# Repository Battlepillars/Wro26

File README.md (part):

<div align="left">

# Table of contents

<ul dir="auto">
    <li><details><summary><a href="#the-team">The team</a></summary>
        <ul dir="auto">
            <li><a href="#nils-stauff">Nils Stauff</a></li>
            <li><a href="#olivia-greilich">Olivia Greilich</a></li>
            <li><a href="#anton-wiesen">Anton Wiesen</a></li>
            <li><a href="#team-photo">Team photo</a></li>
        </ul>
        </details>
      </li>
    <li><a href="#videos-of-the-robot">Videos of the robot</a></li>
    <li><details><summary><a href="#mobility-and-mechanics">1. Mobility and mechanics</a></summary>
        <ul dir="auto">
            <li><a href="#development-goal">Development goal</a></li>
            <li><a href="#chassis-and-mechanical-structure">Chassis and mechanical structure</a>
              <ul dir="auto">
                <li><a href="#chassis-design">Chassis design</a></li>
                <li><a href="#base-deck-iteration">Base deck iteration</a></li>
                <li><a href="#chassis-structure">Chassis structure</a></li>
              </ul>
            </li>
            <li><a href="#drivetrain-concept-and-motor-selection">Drivetrain concept and motor selection</a></li>
            <li><a href="#rear-axle-and-differential">Rear axle and differential</a></li>
            <li><a href="#front-axle-and-steering">Front axle and steering</a>
              <ul dir="auto">
                <li><a href="#ackermann-condition-in-our-steering">Ackermann condition in our steering</a></li>
                <li><a href="#mechanical-precision-of-our-steering">Mechanical precision of our steering</a></li>
                <li><a href="#front-axle-rims-and-tires">Front axle rims and tires</a></li>
              </ul>
            </li>
            <li><a href="#servo-selection-and-position">Servo selection and position</a>
              <ul dir="auto">
                <li><a href="#servo-selection">Servo selection</a></li>
                <li><a href="#servo-position">Servo position</a></li>
              </ul>
            </li>
          </ul>
          </details>
        </li>
        <li><details><summary><a href="#power-and-sensors">2. Power and sensors</a></summary>
        <ul dir="auto">
            <li><a href="#concept">Concept</a></li>
            <li><a href="#electronics-setup">Electronics setup</a></li>
            <li><a href="#camera-use-of-the-camera-and-calibration">Camera: use of the camera and calibration</a>
              <ul dir="auto">
                <li><a href="#use-of-the-camera">Use of the camera</a></li>
                <li><a href="#further-development-rotating-camera-tower">Further development: rotating camera tower</a></li>
                <li><a href="#calibration-procedure">Calibration procedure</a></li>
              </ul>
            </li>
            <li><a href="#distance-sensors">Distance sensors</a>
                <ul dir="auto">
                    <li><a href="#selection-of-distance-sensors">Selection of distance sensors</a></li>
                    <li><a href="#sensor-evaluation">Sensor evaluation</a></li>
                    <li><a href="#sensor-placement-in-the-robot">Sensor placement in the robot</a></li>
                </ul>
            </li>
            <li><a href="#gyro">Gyro</a></li>
            <li><a href="#power-budget-power-supply-and-consumption">Power budget: power supply and consumption</a>
                <ul dir="auto">
                    <li><a href="#worst-case-peak-current-and-regulator-sizing">Worst-case peak current and regulator sizing</a></li>
                    <li><a href="#measured-total-power-requirement">Measured total power requirement</a></li>
                    <li><a href="#runtime-calculation">Runtime calculation</a></li>
                    <li><a href="#avoiding-deep-discharge">Avoiding deep discharge</a></li>
                    <li><a href="#voltage-supply-of-the-individual-components">Voltage supply of the individual components</a></li>
                    <li><a href="#failure-modes-in-sensors-and-power-supply">Failure modes in sensors and power supply</a></li>
                </ul>
            </li>
          </ul>
          </details>
        </li>
        <li><details><summary><a href="#software-development">3. Software development</a></summary>
        <ul dir="auto">
            <li><a href="#software-architecture">Software architecture</a></li>
            <li><a href="#threading-and-system-flow">Threading and system flow</a></li>
            <li><a href="#driving-primitives-in-drivecontrollerpy">Driving primitives in driveController.py</a></li>
            <li><a href="#opening-challenge-driving-strategy">Opening challenge driving strategy</a></li>
            <li><a href="#obstacle-challenge-driving-strategy---strategy-change">Obstacle challenge driving strategy - strategy change</a>
              <ul dir="auto">
                <li><a href="#old-strategy-scanning-while-driving">Old strategy: scanning while driving</a></li>
                <li><a href="#new-strategy-full-scan-fixed-route">New strategy: full scan, fixed route</a></li>
                <li><a href="#passing-two-obstacles-in-one-section">Passing two obstacles in one section</a></li>
                <li><a href="#parking-and-un-parking">Parking and un-parking</a></li>
              </ul>
            </li>
            <li><a href="#serial-communication-and-data-model">Serial communication and data model</a></li>
            <li><a href="#camera-processing">Camera processing</a>
              <ul dir="auto">
                <li><a href="#mask-pipeline">Mask pipeline</a></li>
              </ul>
            </li>
            <li><a href="#software-improvements">Software improvements</a></li>
          </ul>
          </details>
        </li>
        <li><details><summary><a href="#overall-robot-system-and-technical-decisions">4. Overall robot system and technical decisions</a></summary>
        <ul dir="auto">
            <li><a href="#design-constraints">Design constraints</a></li>
            <li><a href="#system-level-risks">System-level risks</a></li>
            <li><a href="#our-robot">Our robot</a></li>
            <li><a href="#technical-specifications">Technical specifications</a></li>
            <li><a href="#system-architecture">System architecture</a></li>
            <li><a href="#key-technical-decisions">Key technical decisions</a>
              <ul dir="auto">
                <li><a href="#raspberry-pi-vs-pure-microcontroller">Raspberry Pi vs. pure microcontroller</a></li>
                <li><a href="#raspberry-pi-5-vs-raspberry-pi-cm5">Raspberry Pi 5 vs. Raspberry Pi CM5</a></li>
                <li><a href="#lidar-vs-time-of-flight-sensors--control-paradigm">LiDAR vs. time-of-flight sensors / control paradigm</a></li>
                <li><a href="#camera-height-and-detection-strategy">Camera height and detection strategy</a></li>
                <li><a href="#chassis-material-pla-vs-ppa-cf">Chassis material: PLA vs. PPA-CF</a></li>
                <li><a href="#gyro-bno055-with-and-without-magnetometer-vs-bno086-without-magnetometer">Gyro: BNO055 with and without magnetometer vs. BNO086 without magnetometer</a></li>
                <li><a href="#rear-axle-ball-differential-vs-rigid-axle">Rear axle: ball differential vs. rigid axle</a></li>
                <li><a href="#tof-sensor-vl53l8cx-vs-tmf8828">ToF sensor: VL53L8CX vs. TMF8828</a></li>
              </ul>
            </li>
            <li><a href="#development-milestones">Development milestones</a></li>
          </ul>
          </details>
        </li>
        <li><details><summary><a href="#5-construction-guide">5. Construction guide</a></summary>
        <ul dir="auto">
            <li><a href="#assembly-overview">Assembly overview</a></li>
            <li><a href="#step-1-preparing-the-3d-printed-parts">Step 1: Preparing the 3D-printed parts</a></li>
            <li><a href="#step-2-lower-deck-assembly">Step 2: Lower deck assembly</a>
              <ul dir="auto">
                <li><a href="#21-drive-motor-and-rear-axle-bearings">2.1 Drive motor and rear-axle bearings</a></li>
                <li><a href="#22-front-axle--steering-knuckles">2.2 Front axle / steering knuckles</a></li>
                <li><a href="#23-rear-axle-front-wheels-and-steering-linkage">2.3 Rear axle, front wheels and steering linkage</a></li>
              </ul>
            </li>
            <li><a href="#step-3-middle-deck-assembly">Step 3: Middle deck assembly</a>
              <ul dir="auto">
                <li><a href="#31-support-bridge-and-middle-deck">3.1 Support bridge and middle deck</a></li>
                <li><a href="#32-mount-the-baseboard-and-connect-all-components">3.2 Mount the baseboard and connect all components</a></li>
              </ul>
            </li>
            <li><a href="#step-4-upper-deck--tof-sensors-and-rotating-camera-tower">Step 4: Upper deck – ToF sensors and rotating camera tower</a>
              <ul dir="auto">
                <li><a href="#41-mount-the-upper-deck">4.1 Mount the upper deck</a></li>
                <li><a href="#42-insert-the-distance-sensors">4.2 Insert the distance sensors</a></li>
                <li><a href="#43-mount-the-camera-tower-and-camera">4.3 Mount the camera tower and camera</a></li>
                <li><a href="#44-connect-the-camera-pan-servo">4.4 Connect the camera pan servo</a></li>
              </ul>
            </li>
            <li><a href="#step-5-wiring">Step 5: Wiring</a></li>
            <li><a href="#step-6-software-installation">Step 6: Software installation</a>
              <ul dir="auto">
                <li><a href="#61-prepare-raspberry-pi-os">6.1 Prepare Raspberry Pi OS</a></li>
                <li><a href="#62-install-python-libraries">6.2 Install Python libraries</a></li>
                <li><a href="#63-install-battlepillars-software">6.3 Install Battlepillars software</a></li>
                <li><a href="#64-build-compile-and-upload-to-the-controllers">6.4 Build, compile and upload to the controllers</a></li>
              </ul>
            </li>
          </ul>
          </details>
        </li>
</ul>

# **The team** 
<div align="center">
    
</div>
In this repository, you’ll find the documentation for the robot created by the "Battlepillars" for the 2026 World Robot Olympiad Future Engineers competition. The robot was the result of a collaborative effort by three students.

## **Nils Stauff**

<div align="center">
    
</div>

Hi! I’m Nils, and I’m 17 years old. I enjoy coding and solving technical problems. In my free time, I like scuba diving and exploring the underwater world. During winter, I often go skiing, and I’m also a big fan of cats.

For our WRO project, I’m responsible for developing the robot’s software and making sure it runs as intended. It can be challenging at times, but it’s very rewarding when everything works as planned!

## **Olivia Greilich**

<div align="center">
    
</div>

Hello everyone! My name is Olivia Greilich and I'm 17, currently attending the Lise-Meitner Gymnasium in Anrath. Languages, communicating and connecting with people is my passion, same with painting, sculpting and crocheting!
One interesting fact about me is that I am simply enamored with jellyfish of all types, colors, shapes and sizes. I have two jellyfish lamps, tons of stickers, books and of course a phone charm.
In my free time, I usually occupy myself with writing fanfiction on Archive Of Our Own (AO3).

My part of the team effort is the documentation and images you'll see below.

## **Anton Wiesen**

<div align="center">
    
</div>

Hello! My name is Anton Wiesen, and I am 16 years old. I am responsible for the mechanical design of the robot and its technical components. My interests mainly lie in designing and building technology for robots. I am also quite experienced with 3D modelling software such as Fusion 360. In my free time, I like hanging out with friends and playing badminton at a sports club.

## **Team photo**

<div align="center">
    
</div>
<br>

# **Videos of the robot**

The following videos show the vehicle operating autonomously, one video per run:

| Run | Link |
|---|---|
| Open Challenge |  |
| Obstacle Challenge |  |

<br><br>

# **Mobility and mechanics**

## **Development goal**
In the 2025 season, we already successfully competed in the Future Engineers category and achieved the highest possible score in both runs at the World Final. 
<br><br>
**The goal for the 2026 season** was no longer just to reliably achieve the maximum score, but to complete the **course in the shortest possible time**. This led to three central mechanical development goals: a smaller and lighter chassis, a faster and more efficient drivetrain, and more precise steering. These goals led to a complete redesign of the chassis, drivetrain, front axle, and electronics layout.
<br><br>
The smaller form factor was meant to bring several advantages: the small size of the car allows for smaller turning radii and therefore higher agility. In addition, during the obstacle challenge, the car has more clearance to obstacles when passing through narrow sections, which makes driving more fault-tolerant and allows for higher speeds.

#### Figure 1: Comparison of the 2025 and 2026 robot designs:

<div align="center">
    
</div>

<br>

## **Chassis and mechanical structure**

### **Chassis design**
The **chassis** was designed in Fusion 360. During development, **plain PLA** was used as filament since it is inexpensive and easy to print. However, the motor mount in PLA did not work reliably, since PLA creeps (deforms under constant pressure), which caused the gear backlash at the motor to drift out of tolerance.
<br><br>
In the final version, the chassis was manufactured from **PPA-CF filament**. PPA-CF is significantly stiffer and does not creep. As a result, the angles of the camera and sensors no longer change due to chassis flex. This improves the reproducibility of the sensor data and provides more consistent readings over the entire run.
<br><br>
However, this created a new problem. If the suspension was not exactly the same height on all sides, or the base deck was slightly warped, a wheel would hover slightly off the ground due to the extreme stiffness of the material and spin freely. In the previous PLA versions, this issue was compensated for by the springy properties of the material. Since we did not want to give up the positive properties of PPA-CF filament with respect to sensor data, we heated the base deck with a heat gun and carefully bent it until all wheels had good ground contact.

#### Table 1: Mechanical iterations in the chassis design:

<table align="center" border="1" style="border-collapse: collapse; border: 2px solid black; margin: 12px 0;">
  <tr>
    <th bgcolor="#4A90C2" style="border: 1px solid black; border-bottom: 3px solid black; padding: 8px; color: white;">Starting version</th>
    <th bgcolor="#4A90C2" style="border: 1px solid black; border-bottom: 3px solid black; padding: 8px; color: white;">Problem</th>
    <th bgcolor="#4A90C2" style="border: 1px solid black; border-bottom: 3px solid black; padding: 8px; color: white;">Observation before</th>
    <th bgcolor="#4A90C2" style="border: 1px solid black; border-bottom: 3px solid black; padding: 8px; color: white;">Change</th>
    <th bgcolor="#4A90C2" style="border: 1px solid black; border-bottom: 3px solid black; padding: 8px; color: white;">Observation after</th>
    <th bgcolor="#4A90C2" style="border: 1px solid black; border-bottom: 3px solid black; padding: 8px; color: white;">Decision</th>
  </tr>
  <tr>
    <td bgcolor="#EAF4FB" style="border: 1px solid black; padding: 8px;">Chassis made of PLA</td>
    <td bgcolor="#EAF4FB" style="border: 1px solid black; padding: 8px;">Motor mount deformed under continuous load, gear backlash drifted out of tolerance</td>
    <td bgcolor="#EAF4FB" style="border: 1px solid black; padding: 8px;">Backlash changed measurably after a few runs (creep), motor ran roughly</td>
    <td bgcolor="#EAF4FB" style="border: 1px solid black; padding: 8px;">Switched filament to PPA-CF</td>
    <td bgcolor="#EAF4FB" style="border: 1px solid black; padding: 8px;">Gear backlash constant, but new problem: wheel hovers slightly off the ground because base deck is too stiff</td>
    <td bgcolor="#EAF4FB" style="border: 1px solid black; padding: 8px;"><b>PPA-CF kept; new problem solved by manually rebending the base deck</b></td>
  </tr>
</table>
<br>

### **Base deck iteration**

At the start, the **base deck** consisted only of a simple rectangle. This first version served to roughly position the most important mechanical components and estimate the required footprint. The dimensions of the rear axle with ball differential, which we purchased as a pre-assembled unit with a fixed rear axle and wheel hubs, served as the initial reference point. This determined the wheelbase and thus the width of the base deck. The length of the base deck, on the other hand, was dictated by the dimensions of our self-developed PCB, since this was the largest component by area and was installed lengthwise in the chassis. For the rear axle we used a ball differential from the model-making sector, since a differential of this size is difficult to print reliably. The base deck was then gradually adapted to the actual mechanical requirements. During this process, more than fifteen versions of the base deck were created and printed until the final version was completed with all necessary cutouts, mounting points, and adaptations for the axles, wheels, sensors, and electronics. A total of ten ball bearings were used for the steering and suspension.

#### Figure 2: Iterations of the base deck:

<div align="center">
    
</div>

### **Chassis structure**

The **chassis is split into three levels**, allowing a compact and clear integration of all components: 
<br>
<li>The base deck carries the drivetrain, battery, differential, and steering.</li>
<li>The middle deck houses the PCB, the Raspberry Pi CM5, the gyroscope, and the microcontroller.
<li>The top deck contains the camera and the ToF sensors.</li>
<br>

The finished vehicle with all components (PCB, battery, Raspberry Pi CM5, sensors, camera) has a **total weight of approx. 400 g**. 
<br>
#### Figure 3: Structure of the robot:

<div align="center">
    
</div>

## **Drivetrain concept and motor selection**

Our goal was to **drive one lap in about 10 seconds** – a race consists of three laps, which we therefore wanted to complete in about 30 seconds. The WRO track has a lap circumference (depending on the track layout) of about 8 m. This results in a required target speed of 8 m / 10 s = 0.8 m/s. However, we cannot drive at full speed permanently. Time is needed for acceleration and braking and for slower cornering. In addition, time is lost for parking and obstacle detection. These factors are hard to calculate, so we estimated a target speed of **2 m/s as the maximum speed** for our car.
<br><br>
Based on the chosen wheels (diameter approx. 27 mm, circumference approx. 84.8 mm), the wheel needs to complete about 23.7 revolutions per second (= 1410 RPM). To achieve the required wheel speed of about 1410 RPM, the gearbox output of the motor must deliver a **speed** of about 3384 RPM, due to the external gear ratio of 2.44:1. That is the first requirement for the motor.
<br><br>
The second requirement concerns **torque**. A motor must not only reach a high speed, but also deliver enough torque to reliably accelerate the vehicle under real conditions. We estimated the required torque based on the vehicle weight of approx. 450 g. Assuming a rolling friction coefficient of 0.05 and a wheel radius of 13.5 mm, this results in:
<br>
<table align="center" width="100%" cellpadding="8" cellspacing="0" border="0"><tr><td bgcolor="#B8D8EE" align="center">
Rolling resistance force: F<sub>roll</sub> = 0.45 kg × 9.81 m/s² × 0.05 ≈ 0.22 N<br>
Torque at the wheel: M<sub>wheel</sub> = 0.22 N × 0.0135 m ≈ 3.0 mNm
</td></tr></table>

Working backward through the external gear ratio, the motor must deliver at least 3.0 / 2.44 ≈ 1.2 mNm of torque, plus reserve for cornering and acceleration.

To find a suitable motor, we bought several small motors of the N20/N30 class that, according to their datasheets, promise high speeds at reasonable torque, and tested these directly in the vehicle. For this we wrote a **test program** that calculates the driving speed via the encoder on the motor. The STM32 reads a quadrature encoder and calculates the rotational speed. The encoder count is converted into a driving speed using the empirically calibrated factor: 

<table align="center" width="100%" cellpadding="8" cellspacing="0" border="0"><tr><td bgcolor="#B8D8EE" align="center">
v [m/s] = encoder count × 30 / (5.165 × 1000)</td></tr></table>

The factor 5.165 was determined from reference measurements over known distances.

 #### Table 2: Comparison of tested motors

<table align="center" border="1" style="border-collapse: collapse; border: 2px solid black;">

  <!-- Table header -->
  <tr>
    <th bgcolor="#4A90C2" width="120" style="border: 1px solid black; border-bottom: 3px solid black; padding: 8px; color: white;">Motor</th>
    <th bgcolor="#4A90C2" width="160" style="border: 1px solid black; border-bottom: 3px solid black; padding: 8px; color: white;">No-load speed<br>(datasheet)</th>
    <th bgcolor="#4A90C2" width="160" style="border: 1px solid black; border-bottom: 3px solid black; padding: 8px; color: white;">Rated torque<br>(datasheet)</th>
    <th bgcolor="#4A90C2" width="160" style="border: 1px solid black; border-bottom: 3px solid black; padding: 8px; color: white;">Measured<br>speed</th>
    <th bgcolor="#4A90C2" width="260" style="border: 1px solid black; border-bottom: 3px solid black; padding: 8px; color: white;">Observations</th>
    <th bgcolor="#4A90C2" width="120" style="border: 1px solid black; border-bottom: 3px solid black; padding: 8px; color: white;">Decision</th>
  </tr>

  <!-- N20 6V 600 rpm -->
  <tr>
    <td bgcolor="#EAF4FB" style="border: 1px solid black; padding: 8px;"><b>N20 6V<br>600 rpm</b></td>
    <td bgcolor="#EAF4FB" style="border: 1px solid black; padding: 8px; text-align: center;">600 rpm</td>
    <td bgcolor="#EAF4FB" style="border: 1px solid black; padding: 8px; text-align: center;">approx. 5 mNm</td>
    <td bgcolor="#EAF4FB" style="border: 1px solid black; padding: 8px; text-align: center;">approx. 0.7 m/s</td>
    <td bgcolor="#EAF4FB" style="border: 1px solid black; padding: 8px;">
      • too slow<br>
      • torque sufficient
    </td>
    <td bgcolor="#EAF4FB" style="border: 1px solid black; padding: 8px; text-align: center;">rejected</td>
  </tr>

  <!-- N20 6V 1500 rpm -->
  <tr>
    <td style="border: 1px solid black; padding: 8px;"><b>N20 6V<br>1500 rpm</b></td>
    <td style="border: 1px solid black; padding: 8px; text-align: center;">1500 rpm</td>
    <td style="border: 1px solid black; padding: 8px; text-align: center;">approx. 2 mNm</td>
    <td style="border: 1px solid black; padding: 8px; text-align: center;">approx. 1.5 m/s</td>
    <td style="border: 1px solid black; padding: 8px;">
      • motor gets very hot<br>
      • torque too low
    </td>
    <td style="border: 1px solid black; padding: 8px; text-align: center;">rejected</td>
  </tr>

  <!-- N30 6V 500 rpm -->
  <tr>
    <td bgcolor="#EAF4FB" style="border: 1px solid black; padding: 8px;"><b>N30 6V<br>500 rpm</b></td>
    <td bgcolor="#EAF4FB" style="border: 1px solid black; padding: 8px; text-align: center;">500 rpm</td>
    <td bgcolor="#EAF4FB" style="border: 1px solid black; padding: 8px; text-align: center;">approx. 9 mNm</td>
    <td bgcolor="#EAF4FB" style="border: 1px solid black; padding: 8px; text-align: center;">approx. 0.8 m/s</td>
    <td bgcolor="#EAF4FB" style="border: 1px solid black; padding: 8px;">
      • high torque<br>
      • speed too low
    </td>
    <td bgcolor="#EAF4FB" style="border: 1px solid black; padding: 8px; text-align: center;">rejected</td>
  </tr>

  <!-- N30 6V 1500 rpm – chosen motor -->
  <tr>
    <td style="border: 1px solid black; border-top: 3px solid black; padding: 8px;"><b>N30 6V<br>1500 rpm</b></td>
    <td style="border: 1px solid black; border-top: 3px solid black; padding: 8px; text-align: center;">1500 rpm</td>
    <td style="border: 1px solid black; border-top: 3px solid black; padding: 8px; text-align: center;">approx. 3 mNm</td>
    <td style="border: 1px solid black; border-top: 3px solid black; padding: 8px; text-align: center;"><b>approx. 2.1 m/s</b></td>
    <td style="border: 1px solid black; border-top: 3px solid black; padding: 8px;">
      • best speed
    </td>
    <td style="border: 1px solid black; border-top: 3px solid black; padding: 8px; text-align: center;"><b>used</b></td>
  </tr>

</table>

We chose the **N30 6V 1500 rpm**, since it achieved the highest real speed in the vehicle at approx. 2 m/s. Its rated torque of approx. 3 mNm is above the calculated minimum requirement of 1.2 mNm and provides sufficient reserve. According to the datasheet it reaches 1500 RPM at 6 V; scaled up to the operating voltage of 11.1 V (3S LiPo), this results in an extrapolated no-load speed of approx. 2775 RPM.  

## **Rear axle and differential**
#### Figure 4: Structure of the rear axle:
<div align="center">
    
</div>

The motor does not drive the rear wheels directly. Instead, we use a **ball differential** on the rear axle. This ball differential was procured as an assembly together with the corresponding Mini-Z wheel hubs and rear wheel rims. Therefore, we use the **Mini-Z rims** that belong to the system on the rear axle, since they are directly compatible with the differential without additional adapters. We use Mini-Z tires on all four wheels.

The N30 motor used is a geared motor with an internal ratio of 10:1. In addition, an external gear pair transmits the power to the rear axle: the drive pinion at the motor output has 18 teeth, the differential gear has 44 teeth, corresponding to a second ratio of 2.44:1. Both figures (10:1 and 2.44:1) are noted in the same power-flow direction motor → gearbox → axle. Overall, this results in a **total reduction** of about 24.4:1 (10:1 × 2.44:1) between the actual electric motor and the rear axle. 

The **rated torque** of the N30 motor is approx. 3 mNm according to the datasheet, after the internal ratio. This is a calculated, not a measured value: scaled up with the external ratio of 2.44:1, this results in an available torque of 3 mNm × 2.44 ≈ 7.3 mNm at the rear axle. 	

The **design** of the rear axle was carried out in Fusion 360 based on the ball differential. One challenge was that both the motor mount and the differential mount had to be manufactured mechanically precisely, so that the gear backlash between the motor pinion and the differential gear was correct. This was practically impossible to achieve by measuring and designing alone, since the dimensional accuracy of the printed parts was not high enough. So the correct distance was determined experimentally by changing the design parameters and reprinting the base deck until it fit. 

#### Table 3: Mechanical iterations in the rear axle design:

<table align="center" border="1" style="border-collapse: collapse; border: 2px solid black; margin: 12px 0;">
  <tr>
    <th bgcolor="#4A90C2" style="border: 1px solid black; border-bottom: 3px solid black; padding: 8px; color: white;">Starting version</th>
    <th bgcolor="#4A90C2" style="border: 1px solid black; border-bottom: 3px solid black; padding: 8px; color: white;">Problem</th>
    <th bgcolor="#4A90C2" style="border: 1px solid black; border-bottom: 3px solid black; padding: 8px; color: white;">Observation before</th>
    <th bgcolor="#4A90C2" style="border: 1px solid black; border-bottom: 3px solid black; padding: 8px; color: white;">Change</th>
    <th bgcolor="#4A90C2" style="border: 1px solid black; border-bottom: 3px solid black; padding: 8px; color: white;">Observation after</th>
    <th bgcolor="#4A90C2" style="border: 1px solid black; border-bottom: 3px solid black; padding: 8px; color: white;">Decision</th>
  </tr>
  <tr>
    <td bgcolor="#EAF4FB" style="border: 1px solid black; padding: 8px;">Calculated nominal distance, base deck version 1</td>
    <td bgcolor="#EAF4FB" style="border: 1px solid black; padding: 8px;">Gear backlash between motor pinion/differential could not be hit purely by calculation (print tolerances)</td>
    <td bgcolor="#EAF4FB" style="border: 1px solid black; padding: 8px;">Gearbox ran roughly, occasionally jammed/rattled</td>
    <td bgcolor="#EAF4FB" style="border: 1px solid black; padding: 8px;">Distance narrowed (1st tightening)</td>
    <td bgcolor="#EAF4FB" style="border: 1px solid black; padding: 8px;">Still rattling/backlash noticeable</td>
    <td bgcolor="#EAF4FB" style="border: 1px solid black; padding: 8px;">Narrow further</td>
  </tr>
  <tr>
    <td bgcolor="#EAF4FB" style="border: 1px solid black; padding: 8px;">Base deck after 1st tightening</td>
    <td bgcolor="#EAF4FB" style="border: 1px solid black; padding: 8px;">Backlash still too large</td>
    <td bgcolor="#EAF4FB" style="border: 1px solid black; padding: 8px;">Rattling reduced but still present</td>
    <td bgcolor="#EAF4FB" style="border: 1px solid black; padding: 8px;">Distance narrowed again (2nd tightening)</td>
    <td bgcolor="#EAF4FB" style="border: 1px solid black; padding: 8px;">Rattling nearly gone, but running slightly less smooth</td>
    <td bgcolor="#EAF4FB" style="border: 1px solid black; padding: 8px;">Narrow further</td>
  </tr>
  <tr>
    <td bgcolor="#EAF4FB" style="border: 1px solid black; padding: 8px;">Base deck after 2nd tightening</td>
    <td bgcolor="#EAF4FB" style="border: 1px solid black; padding: 8px;">Distance still not minimal enough</td>
    <td bgcolor="#EAF4FB" style="border: 1px solid black; padding: 8px;">Slight resistance in the gear mesh</td>
    <td bgcolor="#EAF4FB" style="border: 1px solid black; padding: 8px;">Distance narrowed a third time (3rd tightening)</td>
    <td bgcolor="#EAF4FB" style="border: 1px solid black; padding: 8px;">Gearbox now too tight, occasionally jammed/bound</td>
    <td bgcolor="#EAF4FB" style="border: 1px solid black; padding: 8px;">Widen again</td>
  </tr>
  <tr>
    <td bgcolor="#EAF4FB" style="border: 1px solid black; padding: 8px;">Base deck after 3rd tightening</td>
    <td bgcolor="#EAF4FB" style="border: 1px solid black; padding: 8px;">Distance too small, gearbox binding</td>
    <td bgcolor="#EAF4FB" style="border: 1px solid black; padding: 8px;">Gearbox occasionally jammed/bound</td>
    <td bgcolor="#EAF4FB" style="border: 1px solid black; padding: 8px;">Distance widened again slightly</td>
    <td bgcolor="#EAF4FB" style="border: 1px solid black; padding: 8px;">Quiet, smooth running without rattling/jamming</td>
    <td bgcolor="#EAF4FB" style="border: 1px solid black; padding: 8px;"><b>Final base-deck geometry adopted</b></td>
  </tr>
</table>

## **Front axle and steering**

### Ackermann condition in our steering
For the front axle, as in the previous year, we chose **Ackermann steering**. With simple parallel steering, both front wheels turn by the same angle – in corners this leads to lateral slip, because the inner wheel travels a smaller radius than the outer wheel and would therefore need to turn in more. Ackermann steering solves this problem by designing the steering geometry so that the extended wheel axes of both front wheels intersect at a common point on the extension of the rear axle. The ideal condition for this is:

<table align="center" width="100%" cellpadding="8" cellspacing="0" border="0"><tr><td bgcolor="#B8D8EE" align="center">cot(δ<sub>outer</sub>) − cot(δ<sub>inner</sub>) = track width t / wheelbase L</td></tr></table>

With our track width t = 65 mm and wheelbase L = 80 mm, this results in a **target value of t/L = 0.81.**

Since no suitable off-the-shelf parts were available for our compact form factor, we designed the entire front axle ourselves in Fusion 360 and tested various steering geometry variants via 3D printing. 

#### Figure 5: Adjusting the steering geometry:
<div align="center">
    
</div>

#### Figure 6: Experimental validation of the Ackermann steering geometry using different steering angles and driving curves
<div align="center">
    
</div>

At maximum steering lock, the inner wheel reaches 45° and the outer wheel 35°, which gives:

<table align="center" width="100%" cellpadding="8" cellspacing="0" border="0"><tr><td bgcolor="#B8D8EE" align="center">
cot(35°) − cot(45°) = 1.43 − 1.00 = 0.43
</td></tr></table>

The achieved value of 0.43 is clearly below the ideal value of 0.81. With an unchanged outer angle of 35°, the inner wheel would theoretically need to reach about 58.5° to fully satisfy the Ackermann condition. However, this is not mechanically possible, since the inner wheel is already at its mechanical stop at 45° and a larger angle would exceed the available installation space. Alternatively, with an unchanged inner angle of 45°, the outer angle would need to be reduced to about 29°, which would reduce how sharply the car could turn. The steering therefore only partially satisfies the ideal Ackermann condition. As a result, the extended wheel axes of the front wheels do not intersect exactly at a common turning center, which can more easily cause lateral slip at the front wheels in tight corners:
#### Figure 7: Ackermann condition in our steering:
<div align="center">
    
</div>

The minimum turning radius (measured from the center of the rear axle to the center of the curve) is calculated as follows:

<table align="center" width="100%" cellpadding="8" cellspacing="0" border="0"><tr><td bgcolor="#B8D8EE" align="center">
Minimum turning radius = wheelbase / tan(δ<sub>outer</sub>)
</td></tr></table>

We had not set an exact target turning radius in advance, only the **requirement for the highest possible agility**. For reference: with the alternative possible outer angle of 29° (with an unchanged inner angle of 45°, see above), the minimum turning radius would have been 80 mm / tan(29°) ≈ 144 mm, compared to 114 mm with our actually chosen outer angle of 35°. Even 144 mm would still have been sufficient for the requirements of the WRO track, but would have noticeably reduced agility. We therefore deliberately chose the larger outer angle of 35° and thus decided against fully satisfying the Ackermann condition.

#### Table 4: Steering geometry trade-off – Ackermann compliance vs. agility:

<table align="center" border="1" style="border-collapse: collapse; border: 2px solid black; margin: 12px 0;">
  <tr>
    <th bgcolor="#4A90C2" style="border: 1px solid black; border-bottom: 3px solid black; padding: 8px; color: white;">Criterion</th>
    <th bgcolor="#4A90C2" style="border: 1px solid black; border-bottom: 3px solid black; padding: 8px; color: white;">Ideal Ackermann design</th>
    <th bgcolor="#4A90C2" style="border: 1px solid black; border-bottom: 3px solid black; padding: 8px; color: white;">Variant A:<br>optimal possible Ackermann compliance</th>
    <th bgcolor="#4A90C2" style="border: 1px solid black; border-bottom: 3px solid black; padding: 8px; color: white;">Variant B:<br>higher agility (chosen)</th>
  </tr>
  <tr>
    <td bgcolor="#EAF4FB" style="border: 1px solid black; padding: 8px;"><b>Outer angle δ<sub>outer</sub></b></td>
    <td bgcolor="#EAF4FB" style="border: 1px solid black; padding: 8px; text-align: center;">35°</td>
    <td bgcolor="#EAF4FB" style="border: 1px solid black; padding: 8px; text-align: center;">29°</td>
    <td style="border: 1px solid black; padding: 8px; text-align: center;"><b>35°</b></td>
  </tr>
  <tr>
    <td bgcolor="#EAF4FB" style="border: 1px solid black; padding: 8px;"><b>Inner angle δ<sub>inner</sub></b></td>
    <td bgcolor="#EAF4FB" style="border: 1px solid black; padding: 8px; text-align: center;">58.5°</td>
    <td bgcolor="#EAF4FB" style="border: 1px solid black; padding: 8px; text-align: center;">45° (mechanical cap)</td>
    <td style="border: 1px solid black; padding: 8px; text-align: center;"><b>45° (mechanical cap)</b></td>
  </tr>
  <tr>
    <td bgcolor="#EAF4FB" style="border: 1px solid black; padding: 8px;"><b>Ackermann figure<br>cot δ<sub>outer</sub> − cot δ<sub>inner</sub></b></td>
    <td bgcolor="#EAF4FB" style="border: 1px solid black; padding: 8px; text-align: center;">t/L = 0.81</td>
    <td bgcolor="#EAF4FB" style="border: 1px solid black; padding: 8px; text-align: center;">cot(29°) - cot(45°) = 0.80</td>
    <td style="border: 1px solid black; padding: 8px; text-align: center;"><b>0.43</b></td>
  </tr>
  <tr>
    <td bgcolor="#EAF4FB" style="border: 1px solid black; padding: 8px;"><b>Minimum turning radius</b></td>
    <td bgcolor="#EAF4FB" style="border: 1px solid black; padding: 8px; text-align: center;">n/a</td>
    <td bgcolor="#EAF4FB" style="border: 1px solid black; padding: 8px; text-align: center;">≈ 144 mm</td>
    <td style="border: 1px solid black; padding: 8px; text-align: center;"><b>≈ 114 mm</b></td>
  </tr>
  <tr>
    <td bgcolor="#EAF4FB" style="border: 1px solid black; padding: 8px;"><b>Agility</b></td>
    <td bgcolor="#EAF4FB" style="border: 1px solid black; padding: 8px; text-align: center;">n/a</td>
    <td bgcolor="#EAF4FB" style="border: 1px solid black; padding: 8px; text-align: center;">lower</td>
    <td style="border: 1px solid black; padding: 8px; text-align: center;"><b>higher</b></td>
  </tr>
  <tr>
    <td bgcolor="#EAF4FB" style="border: 1px solid black; border-top: 3px solid black; padding: 8px;"><b>Decision</b></td>
    <td bgcolor="#EAF4FB" style="border: 1px solid black; border-top: 3px solid black; padding: 8px; text-align: center;">not achievable by design</td>
    <td bgcolor="#EAF4FB" style="border: 1px solid black; border-top: 3px solid black; padding: 8px; text-align: center;">rejected</td>
    <td style="border: 1px solid black; border-top: 3px solid black; padding: 8px; text-align: center;"><b>chosen</b></td>
  </tr>
</table>

### Mechanical precision of our steering
However, in addition to the steering geometry, the **mechanical precision of the bearings** is also crucial for whether the calculated angles are actually reproducible during driving. Last year, our car only had one ball bearing per wheel. The steering knuckles were held in plain bearings. As a result, the wheels had noticeable lateral play (about 0.8 mm at the top edge of the wheel, see table) and wobbled back and forth. To minimize steering play, we used a total of eight ball bearings for the front axle bearings. Two per side support the steering knuckles, another two per side support the wheels. These ball bearings ensure precise steering with little play as well as low rolling resistance.

#### Table 5: Mechanical iterations in the front axle bearing:

<table align="center" border="1" style="border-collapse: collapse; border: 2px solid black; margin: 12px 0;">
  <tr>
    <th bgcolor="#4A90C2" style="border: 1px solid black; border-bottom: 3px solid black; padding: 8px; color: white;">Starting version</th>
    <th bgcolor="#4A90C2" style="border: 1px solid black; border-bottom: 3px solid black; padding: 8px; color: white;">Problem</th>
    <th bgcolor="#4A90C2" style="border: 1px solid black; border-bottom: 3px solid black; padding: 8px; color: white;">Measured value before</th>
    <th bgcolor="#4A90C2" style="border: 1px solid black; border-bottom: 3px solid black; padding: 8px; color: white;">Change</th>
    <th bgcolor="#4A90C2" style="border: 1px solid black; border-bottom: 3px solid black; padding: 8px; color: white;">Measured value after</th>
    <th bgcolor="#4A90C2" style="border: 1px solid black; border-bottom: 3px solid black; padding: 8px; color: white;">Decision</th>
  </tr>
  <tr>
    <td bgcolor="#EAF4FB" style="border: 1px solid black; padding: 8px;">Plain-bearing steering knuckles + 1 ball bearing/wheel (2025 season)</td>
    <td bgcolor="#EAF4FB" style="border: 1px solid black; padding: 8px;">Front wheels had lateral play, steering angle not reproducible while driving</td>
    <td bgcolor="#EAF4FB" style="border: 1px solid black; padding: 8px;">≈ 0.8 mm (corresponds to ≈ 2.5° tilt play)</td>
    <td bgcolor="#EAF4FB" style="border: 1px solid black; padding: 8px;">Switched to 8 ball bearings (2× steering knuckle + 2× wheel per side)</td>
    <td bgcolor="#EAF4FB" style="border: 1px solid black; padding: 8px;">&lt; 0.1 mm (no longer noticeable)</td>
    <td bgcolor="#EAF4FB" style="border: 1px solid black; padding: 8px;"><b>8-ball-bearing solution adopted</b></td>
  </tr>
</table>

<sub><b>Measurement method (lateral wheel play):</b> Vehicle fixed, wheel aligned straight. The wheel is pushed by hand (without tools) alternately inward and outward at the top edge until the noticeable play limit is reached. The total lateral deflection at the top edge of the wheel is measured with a caliper against a fixed reference point. The conversion to a tilt angle is done via the wheel radius (≈ 18 mm): angle = arctan(deflection / wheel radius). The average of n = 5 measurements is given.</sub>

#### Figure 8: Cross-section of the front axle (top: angled cut, bottom: straight cut):
<div align="center">
    
    <br><sub>Angled cut: the four ball bearings per steering-knuckle side (marked in red) are visible, which support the steering knuckle (steering motion).</sub>
</div>
<br><br>
<div align="center">
    
    <br><sub>Straight cut: the ball bearings of the wheel suspension (wheel axle) are visible, in addition to the steering-knuckle bearings in the left image.</sub>
</div>
<br>

### Front axle rims and tires
Since the front axle was fully designed by us, we do not use Mini-Z rims there, but **our own 3D-printed rims**. These were dimensioned so that the same Mini-Z tires used on the rear axle could be mounted on them. This means that all four wheels use the same tire type, while the rims are each adapted to the design of the front or rear axle respectively.

## **Servo selection and position**

### Servo selection
When **selecting** the steering servo, besides the size, quick availability was the main deciding factor. Initially, a particularly compact and inexpensive servo (approx. €2) with an all-plastic gearbox was used. However, the pronounced steering play of about 5° (measured, see table) proved insufficient for precise control, which is why the **INJORA N30 Nano** with a coreless motor, metal gearbox, and aluminum housing was chosen as a replacement. At 7 g and dimensions of 15.2 × 13.0 × 21.3 mm, it remains extremely compact; at 6 V it provides a torque of 1.3 kg·cm at an actuation speed of 0.05 s/60°. Since the force and reaction-time requirements in this application are low, almost any commercially available servo would have met the specification – the only decisive factor was the backlash-free metal gearbox.

#### Table 6: Mechanical iterations in the steering servo selection:

<table align="center" border="1" style="border-collapse: collapse; border: 2px solid black; margin: 12px 0;">
  <tr>
    <th bgcolor="#4A90C2" style="border: 1px solid black; border-bottom: 3px solid black; padding: 8px; color: white;">Starting version</th>
    <th bgcolor="#4A90C2" style="border: 1px solid black; border-bottom: 3px solid black; padding: 8px; color: white;">Problem</th>
    <th bgcolor="#4A90C2" style="border: 1px solid black; border-bottom: 3px solid black; padding: 8px; color: white;">Measured value before</th>
    <th bgcolor="#4A90C2" style="border: 1px solid black; border-bottom: 3px solid black; padding: 8px; color: white;">Change</th>
    <th bgcolor="#4A90C2" style="border: 1px solid black; border-bottom: 3px solid black; padding: 8px; color: white;">Measured value after</th>
    <th bgcolor="#4A90C2" style="border: 1px solid black; border-bottom: 3px solid black; padding: 8px; color: white;">Decision</th>
  </tr>
  <tr>
    <td bgcolor="#EAF4FB" style="border: 1px solid black; padding: 8px;">Compact servo with plastic gearbox (approx. €2)</td>
    <td bgcolor="#EAF4FB" style="border: 1px solid black; padding: 8px;">All-plastic gearbox showed noticeable steering play, leading to imprecise steering control</td>
    <td bgcolor="#EAF4FB" style="border: 1px solid black; padding: 8px;">≈ 5° (Δs ≈ 9 mm at r = 100 mm)</td>
    <td bgcolor="#EAF4FB" style="border: 1px solid black; padding: 8px;">Replaced with INJORA N30 Nano with metal gearbox</td>
    <td bgcolor="#EAF4FB" style="border: 1px solid black; padding: 8px;">≤ 1° (Δs ≤ 1.7 mm at r = 100 mm)</td>
    <td bgcolor="#EAF4FB" style="border: 1px solid black; padding: 8px;"><b>INJORA N30 Nano adopted</b></td>
  </tr>
</table>

<sub><b>Measurement method (steering play):</b> The servo is powered and actively holds the center position. A long, rigid pointer (e.g. a skewer, effective radius r = 100 mm) is attached to the steering arm/wheel. The wheel is pushed by hand with low force alternately in both directions until the noticeable play limit is reached, and the total lateral deflection Δs at the pointer tip is read against a fixed scale. The play angle results as angle = arctan(Δs / r). The average of n = 5 measurements is given.</sub>

### Servo position
The **positioning of the servo** presented an independent design challenge. The arrangement common in model vehicles – servo and linkage centered in the vehicle – was ruled out, because we needed a relatively short wheelbase for high agility and wanted to fit the battery between the front and rear wheels for a low center of gravity. After evaluating numerous configurations, the servo was moved in front of the front axle, with the linkage routed behind it. This allowed the bumper area to be used constructively without having to relocate the battery or the PCB; the center of gravity remained low and central, and the required steering lock was achieved without collisions.

<table width="100%" cellpadding="10" cellspacing="0" border="0"><tr><td bgcolor="#2E8B57" width="1%">&nbsp;</td><td bgcolor="#E2F3E5">
 <b>Result:</b> Ball-bearing front axle, metal-gear servo, and the new steering geometry together reduce the minimum turning radius from <b>172 mm to 114 mm</b> and eliminate noticeable steering play compared to the 2025 season.
</td></tr></table>

<br>

# **Power and sensors**

## **Concept**
To achieve the design goal of a small and fast vehicle, a fundamental overhaul of the electronics was necessary. The previous year's system used an RPLiDAR S2 for environment detection as well as two optical odometry sensors for position determination. Control was entirely coordinate-based – driving commands effectively read "go to coordinate X/Y". However, the LiDAR only provided ~10 updates per second with a delay of 100–200 ms, which meant position corrections only worked reliably while stationary. Odometry took over position tracking while driving, but limited the maximum speed to 0.5 m/s – above that, its measurements became unreliable.

For the new vehicle we therefore chose a fundamentally different approach: several **time-of-flight sensors** (VL53L8CX) continuously measure the distances to the walls at 30 Hz, enabling control without stopping. The control logic is now event-based – instead of "go to coordinate X/Y", a driving command now reads, for example, "drive toward the wall until the distance is 20 cm". Since no more stops are needed for position correction, the vehicle drives noticeably more smoothly and faster.

<table width="100%" cellpadding="10" cellspacing="0" border="0"><tr><td bgcolor="#2E8B57" width="1%">&nbsp;</td><td bgcolor="#E2F3E5">
 <b>Result:</b> The average time for a run in the obstacle challenge dropped from <b>160 s (2025)</b> to <b>35–45 s (2026)</b> – an improvement of about a factor of 4. The design goal of 30 s per run was thus narrowly missed.
</td></tr></table>
<br>

## **Electronics setup**

For the electronics, a test setup was first built on a **breadboard**. This allowed us to check whether the key components fundamentally worked before having our own PCB manufactured. Among other things, we tested the microcontroller, motor, motor encoder, motor driver, servo, time-of-flight sensors, and camera.

We developed the **PCB (baseboard)** ourselves using the open-source EDA tool **KiCad** (project files: <code>kicad/baseboard</code>). It is a two-layer PCB (2 copper layers) connected directly to the Raspberry Pi CM5 via a Hirose FH12-22S high-speed connector. It also carries the STM32F411, the voltage regulators, and the connectors for the motor, servo, gyroscope, and ToF sensors. The manufacturing files (Gerber data, bill of materials, position data) were exported with a KiCad fabrication-toolkit plugin (see <code>kicad/baseboard/production</code>); manufacturing and assembly were done externally. 

The complete electronics setup is shown in the wiring diagram below, which shows all connections between the baseboard, Raspberry Pi CM5, STM32, sensors, motor driver, and servo.

#### Figure 9: Wiring diagram

</div><div align="center">
    
</div>

## **Camera: use of the camera and calibration**

### **Use of the camera** 
As in the previous year, we use the **Raspberry Pi Camera Module 3 Wide (12 MP)**, since it has proven itself.

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
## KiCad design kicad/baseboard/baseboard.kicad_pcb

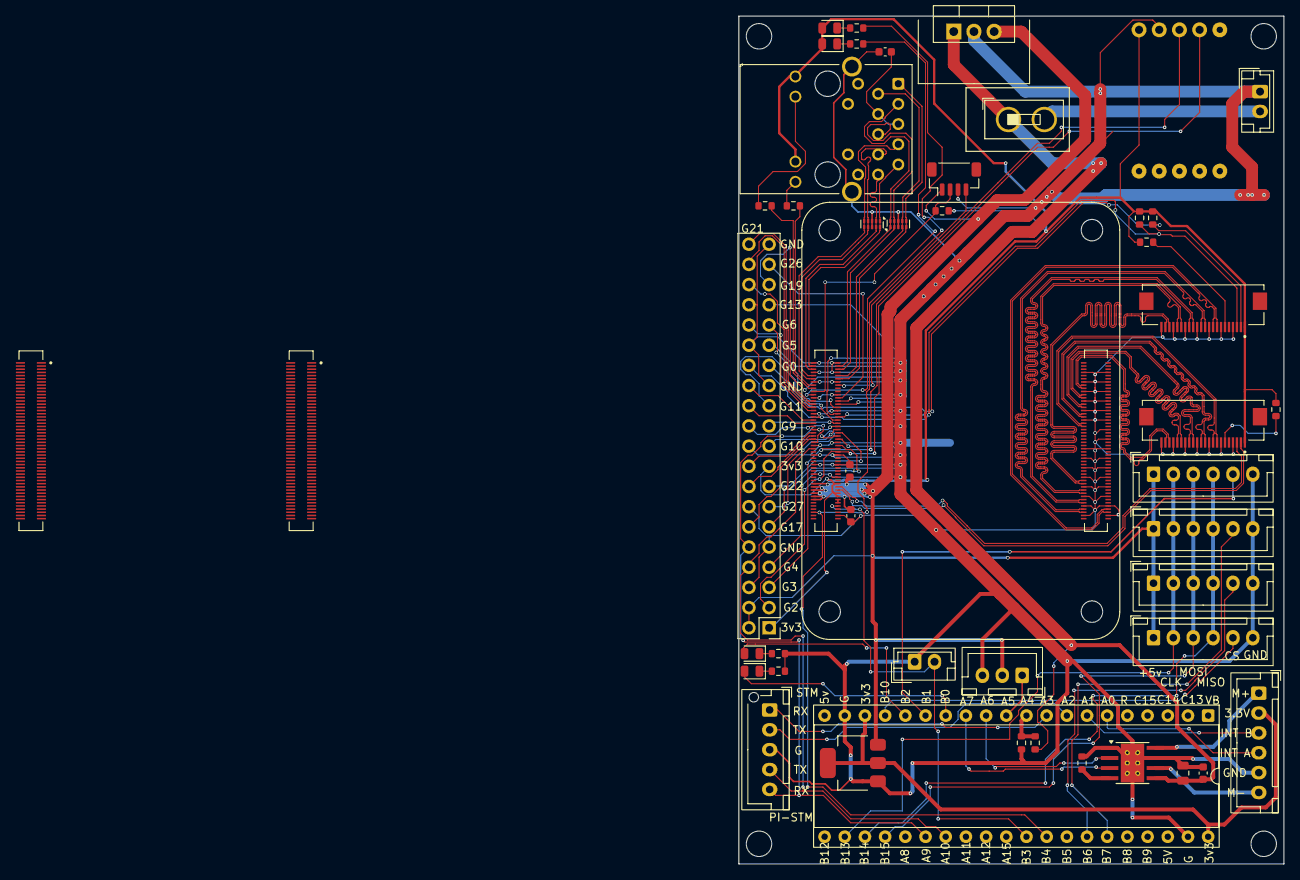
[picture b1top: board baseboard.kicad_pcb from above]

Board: 2 copper layers, 68.6 x 106.7 mm, 52 parts (0 on the bottom side), 101 nets.

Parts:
C1, C9, C18: 100n; C_0603_1608Metric
C4: 0.1uF/15V; C_0603_1608Metric
C5: 22uF/15V; C_0805_2012Metric
D1: LED Red; LED_0805_2012Metric
D2, D3, D4: LED Green; LED_0805_2012Metric
H1, H2, H3, H4: MountingHole; MountingHole_3.2mm_M3_DIN965
J1, J4, J7, J10, J12: Conn_01x06_Pin; JST_XH_B6B-XH-A_1x06_P2.50mm_Vertical
J2, J6: 10164227-1001A1RLF; AMPHENOL_10164227-1001A1RLF
J3, J11: Conn_01x02_Pin; JST_EH_B2B-EH-A_1x02_P2.50mm_Vertical
J5, J16: Conn_01x22_Female; AMPHENOL_F305-1A7H1-21022-E100
J8: THD-20-R; PinHeader_2x20_P2.54mm_Vertical
J14: JST_SHBM04B-SRSS-TB; JST_SH_BM04B-SRSS-TB_1x04-1MP_P1.00mm_Vertical
J15: Conn_01x03_Pin; JST_XH_B3B-XH-A_1x03_P2.50mm_Vertical
J17: DfRobot BNO055
J18: Conn_01x05; JST_XH_B5B-XH-AM_1x05_P2.50mm_Vertical
Module1: ComputeModule5-CM5; Raspberry-Pi-5-Compute-Module
R1, R4, R5, R10, R12: 1k; R_0603_1608Metric
R2, R3: 470R; R_0603_1608Metric
R6, R7, R8, R14: 2.2K 1%; R_0603_1608Metric
R9: 4k7; R_0603_1608Metric
R11: 10K 1%; R_0603_1608Metric
R13: 30k; R_0603_1608Metric
SW1: SW_SPST; SW_DIP_SPSTx01_Slide_9.78x4.72mm_W7.62mm_P2.54mm
U1, U2: TPD4EUSB30; USON-10_2.5x1.0mm_P0.5mm
U3: MagJack-A70-112-331N126; TRJG0926HENL
U6: STM32F411_BlackPill; DIP-40_W15.24mm_Socket
U7: DRV8871DDA; Texas_HTSOP-8-1EP_3.9x4.9mm_P1.27mm_EP2.95x4.9mm_Mask2.4x3.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
U8: AMS1117-3.3; SOT-223-3_TabPin2
U9: L7805; TO-220-3_Vertical

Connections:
+5v: C9.1, C18.1, J1.1, J4.1, J8.2, J8.4, J10.1, J12.1, J14.1, J15.2, Module1.77 (+5v_(Input)), Module1.79 (+5v_(Input)), Module1.81 (+5v_(Input)), Module1.83 (+5v_(Input)), Module1.85 (+5v_(Input)), Module1.87 (+5v_(Input)), U8.3 (VIN), U9.3 (OUT)
/+3.3v: D1.2 (A), D2.2 (A), J5.1, J8.1, J8.17, J16.1, J17.1 (VCC_33), Module1.78 (GPIO_VREF(1.8v/3.3v_Input)), Module1.84 (+3.3v_(Output)), Module1.86 (+3.3v_(Output)), R6.1, R7.1, R8.1, R11.1, R14.1, U3.15 (LEDY_A), U3.17 (LEDG_A)
/CM5_GPIO ( Ethernet, GPIO, SDCARD)/+1.8v: Module1.88 (+1.8v_(Output)), Module1.90 (+1.8v_(Output))
/CM5_GPIO ( Ethernet, GPIO, SDCARD)/ETH_LEDG: Module1.17 (Ethernet_nLED2(3.3v)), R2.2
/CM5_GPIO ( Ethernet, GPIO, SDCARD)/ETH_LEDY: Module1.15 (Ethernet_nLED3(3.3v)), R3.2
/CM5_GPIO ( Ethernet, GPIO, SDCARD)/GPIO2: J8.3, J17.4 (SDA), Module1.58 (GPIO2)
/CM5_GPIO ( Ethernet, GPIO, SDCARD)/GPIO3: J8.5, J17.3 (SCL), Module1.56 (GPIO3)
/CM5_GPIO ( Ethernet, GPIO, SDCARD)/GPIO4: J8.7, Module1.54 (GPIO4)
/CM5_GPIO ( Ethernet, GPIO, SDCARD)/GPIO5: J8.29, Module1.34 (GPIO5)
/CM5_GPIO ( Ethernet, GPIO, SDCARD)/GPIO6: J8.31, Module1.30 (GPIO6)
/CM5_GPIO ( Ethernet, GPIO, SDCARD)/GPIO7: J8.26, Module1.37 (GPIO7)
/CM5_GPIO ( Ethernet, GPIO, SDCARD)/GPIO8: J8.24, Module1.39 (GPIO8)
/CM5_GPIO ( Ethernet, GPIO, SDCARD)/GPIO9: J8.21, Module1.40 (GPIO9)
/CM5_GPIO ( Ethernet, GPIO, SDCARD)/GPIO10: J8.19, Module1.44 (GPIO10)
/CM5_GPIO ( Ethernet, GPIO, SDCARD)/GPIO11: J8.23, Module1.38 (GPIO11)
/CM5_GPIO ( Ethernet, GPIO, SDCARD)/GPIO12: J8.32, Module1.31 (GPIO12)
/CM5_GPIO ( Ethernet, GPIO, SDCARD)/GPIO13: J8.33, Module1.28 (GPIO13)
/CM5_GPIO ( Ethernet, GPIO, SDCARD)/GPIO16: J8.36, Module1.29 (GPIO16)
/CM5_GPIO ( Ethernet, GPIO, SDCARD)/GPIO17: J8.11, Module1.50 (GPIO17)
/CM5_GPIO ( Ethernet, GPIO, SDCARD)/GPIO18: J8.12, Module1.49 (GPIO18)
/CM5_GPIO ( Ethernet, GPIO, SDCARD)/GPIO19: J8.35, Module1.26 (GPIO19)
/CM5_GPIO ( Ethernet, GPIO, SDCARD)/GPIO20: J8.38, Module1.27 (GPIO20)
/CM5_GPIO ( Ethernet, GPIO, SDCARD)/GPIO21: J8.40, Module1.25 (GPIO21)
/CM5_GPIO ( Ethernet, GPIO, SDCARD)/GPIO22: J8.15, Module1.46 (GPIO22)
/CM5_GPIO ( Ethernet, GPIO, SDCARD)/GPIO23: J8.16, Module1.47 (GPIO23)
/CM5_GPIO ( Ethernet, GPIO, SDCARD)/GPIO24: J8.18, Module1.45 (GPIO24)
/CM5_GPIO ( Ethernet, GPIO, SDCARD)/GPIO25: J8.22, Module1.41 (GPIO25)
/CM5_GPIO ( Ethernet, GPIO, SDCARD)/GPIO26: J8.37, Module1.24 (GPIO26)
/CM5_GPIO ( Ethernet, GPIO, SDCARD)/GPIO27: J8.13, Module1.48 (GPIO27)
/CM5_GPIO ( Ethernet, GPIO, SDCARD)/ID_SC: J8.28, J16.3, Module1.35 (ID_SC), R7.2
/CM5_GPIO ( Ethernet, GPIO, SDCARD)/ID_SD: J8.27, J16.2, Module1.36 (ID_SD), R6.2
/CM5_GPIO ( Ethernet, GPIO, SDCARD)/PWM: J14.2, Module1.19 (FAN_PWM), R11.2
/CM5_GPIO ( Ethernet, GPIO, SDCARD)/TACHO: J14.4, Module1.16 (FAN_TACHO)
/CM5_GPIO ( Ethernet, GPIO, SDCARD)/TRD0_N: Module1.10 (Ethernet_Pair0_N), U2.4 (D2+), U2.7, U3.2 (TRD0-)
/CM5_GPIO ( Ethernet, GPIO, SDCARD)/TRD0_P: Module1.12 (Ethernet_Pair0_P), U2.5 (D2-), U2.6, U3.1 (TRD0+)
/CM5_GPIO ( Ethernet, GPIO, SDCARD)/TRD1_N: Module1.6 (Ethernet_Pair1_N), U2.2 (D1-), U2.9, U3.6 (TRD1-)
/CM5_GPIO ( Ethernet, GPIO, SDCARD)/TRD1_P: Module1.4 (Ethernet_Pair1_P), U2.1 (D1+), U2.10, U3.3 (TRD1+)
/CM5_GPIO ( Ethernet, GPIO, SDCARD)/TRD2_N: Module1.9 (Ethernet_Pair2_N), U1.4 (D2+), U1.7, U3.8 (TRD2-)
/CM5_GPIO ( Ethernet, GPIO, SDCARD)/TRD2_P: Module1.11 (Ethernet_Pair2_P), U1.5 (D2-), U1.6, U3.7 (TRD2+)
/CM5_GPIO ( Ethernet, GPIO, SDCARD)/TRD3_N: Module1.5 (Ethernet_Pair3_N), U1.2 (D1-), U1.9, U3.10 (TRD3-)
/CM5_GPIO ( Ethernet, GPIO, SDCARD)/TRD3_P: Module1.3 (Ethernet_Pair3_P), U1.1 (D1+), U1.10, U3.9 (TRD3+)
/CM5_HighSpeed/DPHY0_C_N: J5.15, Module1.127 (MIPI0_C_N)
/CM5_HighSpeed/DPHY0_C_P: J5.14, Module1.129 (MIPI0_C_P)
/CM5_HighSpeed/DPHY0_D0_N: J5.21, Module1.115 (MIPI0_D0_N)
/CM5_HighSpeed/DPHY0_D0_P: J5.20, Module1.117 (MIPI0_D0_P)
/CM5_HighSpeed/DPHY0_D1_N: J5.18, Module1.121 (MIPI0_D1_N)
/CM5_HighSpeed/DPHY0_D1_P: J5.17, Module1.123 (MIPI0_D1_P)
/CM5_HighSpeed/DPHY0_D2_N: J5.12, Module1.133 (MIPI0_D2_N)
/CM5_HighSpeed/DPHY0_D2_P: J5.11, Module1.135 (MIPI0_D2_P)
/CM5_HighSpeed/DPHY0_D3_N: J5.9, Module1.139 (MIPI0_D3_N)
/CM5_HighSpeed/DPHY0_D3_P: J5.8, Module1.141 (MIPI0_D3_P)
/CM5_HighSpeed/DPHY1_C_N: J16.15, Module1.187 (MIPI1_C_N)
/CM5_HighSpeed/DPHY1_C_P: J16.14, Module1.189 (MIPI1_C_P)
/CM5_HighSpeed/DPHY1_D0_N: J16.21, Module1.175 (MIPI1_D0_N)
/CM5_HighSpeed/DPHY1_D0_P: J16.20, Module1.177 (MIPI1_D0_P)
/CM5_HighSpeed/DPHY1_D1_N: J16.18, Module1.181 (MIPI1_D1_N)
/CM5_HighSpeed/DPHY1_D1_P: J16.17, Module1.183 (MIPI1_D1_P)
/CM5_HighSpeed/DPHY1_D2_N: J16.12, Module1.193 (MIPI1_D2_N)
/CM5_HighSpeed/DPHY1_D2_P: J16.11, Module1.195 (MIPI1_D2_P)
/CM5_HighSpeed/DPHY1_D3_N: J16.9, Module1.194 (MIPI1_D3_N)
/CM5_HighSpeed/DPHY1_D3_P: J16.8, Module1.196 (MIPI1_D3_P)
/CM5_HighSpeed/SCL0: J5.3, Module1.80 (SCL0)
/CM5_HighSpeed/SDA0: J5.2, Module1.82 (SDA0)
/stm32/3.3v micro: J7.2, U6.18 (3.3V), U6.40 (3,3V), U8.2 (VOUT)
/stm32/CS1: J12.5, U6.17 (PB10)
/stm32/CS2: J10.5, U6.15 (PB1)
/stm32/CS3: J4.5, U6.35 (B7)
/stm32/CS4: J1.5, U6.34 (B6)
/stm32/MOTOR INT A: J7.4, U6.6 (PA0)
/stm32/MOTOR INT B: J7.3, U6.7 (PA1)
/stm32/MOTOR PWM 1: U6.13 (PA7), U7.3 (IN1)
/stm32/MOTOR PWM 2: U6.12 (PA6), U7.2 (IN2)
/stm32/SPI CLK: J1.2, J4.2, J10.2, J12.2, U6.22 (B13)
/stm32/SPI MISO: J1.4, J4.4, J10.4, J12.4, U6.23 (B14)
/stm32/SPI MOSI: J1.3, J4.3, J10.3, J12.3, U6.24 (B15)
BatterieSwitch: C4.2, C5.2, R9.2, SW1.1 (A), U7.5 (VM), U9.1 (IN)
GND: C1.2, C4.1, C5.1, C9.2, C18.2, J1.6, J3.1, J4.6, J5.4, J5.7, J5.10, J5.13, J5.16, J5.19, J5.22, J7.5, J8.6, J8.9, J8.14, J8.20, J8.25, J8.30, J8.34, J8.39, J10.6, J11.1, J12.6, J14.3, J15.3, J16.4, J16.7, J16.10, J16.13, J16.16, J16.19, J16.22, J17.2 (GND), J18.3, Module1.1 (GND), Module1.2 (GND), Module1.7 (GND), Module1.8 (GND), Module1.13 (GND), Module1.14 (GND), Module1.22 (GND), Module1.23 (GND), Module1.32 (GND), Module1.33 (GND), Module1.42 (GND), Module1.43 (GND), Module1.52 (GND), Module1.53 (GND), Module1.59 (GND), Module1.60 (GND), Module1.65 (GND), Module1.66 (GND), Module1.71 (GND), Module1.74 (GND), Module1.98 (GND), Module1.107 (GND), Module1.108 (GND), Module1.113 (GND), Module1.114 (GND), Module1.119 (GND), Module1.120 (GND), Module1.125 (GND), Module1.126 (GND), Module1.131 (GND), Module1.132 (GND), Module1.137 (GND), Module1.138 (GND), Module1.144 (GND), Module1.150 (GND), Module1.155 (GND), Module1.156 (GND), Module1.161 (GND), Module1.162 (GND), Module1.167 (GND), Module1.168 (GND), Module1.173 (GND), Module1.174 (GND), Module1.179 (GND), Module1.180 (GND), Module1.185 (GND), Module1.186 (GND), Module1.191 (GND), Module1.192 (GND), Module1.197 (GND), Module1.198 (GND), R4.2, R5.2, R12.2, R13.2, U1.3 (GND), U1.8 (GND), U2.3 (GND), U2.8 (GND), U3.19 (SHIELD), U3.20 (SHIELD), U6.19 (GND), U6.39 (GND), U7.1 (GND), U7.7 (GND), U7.9 (GND), U8.1 (GND/ADJ), U9.2 (GND)
unnamed: C1.1, U3.4 (CT), U3.5 (CT)
unnamed: D1.1 (K), R10.1
unnamed: D2.1 (K), R1.1
unnamed: D3.2 (A), U6.16 (PB2)
unnamed: D3.1 (K), R4.1
unnamed: D4.2 (A), U6.14 (PB0)
unnamed: D4.1 (K), R5.1
unnamed: J5.6, R14.2
unnamed: J7.1, U7.8 (OUT2)
unnamed: J7.6, U7.6 (OUT1)
unnamed: J11.2, SW1.2 (B)
unnamed: J15.1, U6.11 (PA5)
unnamed: J16.6, R8.2
unnamed: J18.1, U6.9 (PA3)
unnamed: J18.2, U6.8 (PA2)
unnamed: Module1.21 (LED_nACT), R1.2
unnamed: R3.1, U3.18 (LEDG_K)
unnamed: R2.1, U3.16 (LEDY_K)
unnamed: R9.1, R12.1, U6.10 (PA4)
unnamed: R13.1, U7.4 (ILIM)
PWR_BUT: J3.2, Module1.92 (PWR_BUT), U6.31 (B3)
Stm32 Serial RX: J8.8, J18.4, Module1.55 (GPIO14), U6.27 (A10)
Stm32 Serial TX: J8.10, J18.5, Module1.51 (GPIO15), U6.26 (A9)
nPWR_LED: Module1.95 (LED_nPWR), R10.2, U6.32 (B4)

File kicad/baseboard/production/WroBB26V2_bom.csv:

Designator,Footprint,Quantity,Value,LCSC Part #
"C1, C18, C9",0603,3,100n,C14663
C4,0603,1,0.1uF/15V,C14663
C5,0805,1,22uF/15V,C45783
D1,0805,1,LED Red,C84256
D2,0805,1,LED Green,C2297
D3,0805,1,LED Green,
D4,0805,1,LED Green,C2296
"J1, J10, J12, J4, J7",JST_XH_B6B-XH-A_1x06_P2.50mm_Vertical,5,Conn_01x06_Pin,C160255
"J11, J3",JST_EH_B2B-EH-A_1x02_P2.50mm_Vertical,2,Conn_01x02_Pin,
J14,JST_SH_BM04B-SRSS-TB_1x04-1MP_P1.00mm_Vertical,1,JST_SHBM04B-SRSS-TB,C160390
J15,JST_XH_B3B-XH-A_1x03_P2.50mm_Vertical,1,Conn_01x03_Pin,
"J16, J5",AMPHENOL_F305-1A7H1-21022-E100,2,Conn_01x22_Female,C3168287
J17,DfRobot BNO055,1,DfRobot BNO055,
J18,JST_XH_B5B-XH-AM_1x05_P2.50mm_Vertical,1,Conn_01x05,
"J2, J6",AMPHENOL_10164227-1001A1RLF,2,10164227-1001A1RLF,C7435219
J8,PinHeader_2x20_P2.54mm_Vertical,1,THD-20-R,
MODULE1,Raspberry-Pi-5-Compute-Module,1,ComputeModule5-CM5,
"R1, R10, R12, R4, R5",0603,5,1k,C21190
R11,0603,1,10K 1%,C25804
R13,0603,1,30k,C22984
R14,0603,1,2.2K 1%,LCSC Part #
"R2, R3",0603,2,470R,C23179
"R6, R7, R8",0603,3,2.2K 1%,C4190
R9,0603,1,4k7,C23162
SW1,SW_DIP_SPSTx01_Slide_9.78x4.72mm_W7.62mm_P2.54mm,1,SW_SPST,
"U1, U2",USON-10_2.5x1.0mm_P0.5mm,2,TPD4EUSB30,C90627
U3,TRJG0926HENL,1,MagJack-A70-112-331N126,C22457393
U6,DIP-40_W15.24mm_Socket,1,STM32F411_BlackPill,
U7,Texas_HTSOP-8-1EP_3.9x4.9mm_P1.27mm_EP2.95x4.9mm_Mask2.4x3.1mm_ThermalVias,1,DRV8871DDA,C75864
U8,SOT-223-3_TabPin2,1,AMS1117-3.3,C6186

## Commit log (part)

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2026-02-17 Add Baseboard Kicad project
2026-02-19 Baseboard partial routing
2026-02-20 Finish PCB routing
2026-02-20 Setup baseboard pcb production settings
2026-02-21 Last production adjustments
2026-03-12 Correct V1 mistakes : Turned MISO, Correct STM32 template. Add BMO055 Gyroskope . Add servo connector. Add serial port connector. Add Pi - Stm32 serial connection. Add Silkscreen texts.
2026-03-12 Add V2 production files
2026-03-12 First draft of communication protocol
2026-03-24 Tune pid controller, expand communication protocol
2026-03-31 Add command parsing to stm32
2026-03-31 Pi tof camera parsing and basic ui display
2026-04-01 Fix Parser Bug
2026-04-01 Basic UI, first draft drive controller
2026-04-02 Implement PID controller for steering and enhance drive controller functionality
2026-04-06 Add configuration files for PlatformIO and update main.cpp for sensor initialization
2026-04-08 first openchallenge draft
2026-04-08 Test tof in 4x4 instead of 8x8
2026-04-10 Add camera module for color-based obstacle detection and integrate with drive controller, add first obsta le avoidance test
2026-04-23 -Enhance camera and drive controller functionality for obstacle detection and navigation - Modified DriveController to include new methods for setting commands and adjusting speed and heading. - Impr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
2026-04-28 add tof-sensor 5 and 6, advance obstacle course
2026-04-28 Update .gitignore to include additional cache and capture files
2026-05-07 added Camera Testing function, added obstacle Challenge Single
2026-05-09 bugfix and update gitignore
2026-05-11 Refactor camera and drive controller for improved obstacle detection and logging; update .gitignore and UI display
2026-05-11 Add launch configuration for Python debugging over Remote SSH
2026-05-11 Add functionality to scan all obstacles at the beginning
2026-05-11 implement all color detections at race start; update singleScan function to utilize new methods
2026-05-13 Added independent monitor for temperature and runtime
2026-05-13 Refactor gyro handling and logging; update wall drive logic and UI display
2026-05-13 Add gyro rate calibration
2026-05-13 Enhance sensor initialization and add support for additional sensors in main.cpp
2026-05-13 Update .gitignore to include PlatformIO configuration files and directories
2026-05-13 Reduce SPI busspeed and sensor update rate to prevent sensor dropouts
2026-05-14 Add launch configuration for Python debugging in VSCode
2026-05-15 - Enhanced `DriveController` with improved heading normalization and added `tightTurn` method for better maneuverability. - Introduced `gyroBNO085` class for interfacing with the BNO085 IMU, - Update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
2026-05-16 Disable physically damaged sensors
2026-05-17 add openChallenge direction finding
2026-05-17 Add button to start driving
2026-05-17 Add bno086 subburt, add startbutton support to py software
2026-05-21 Add autoChallenge functionality to main program
2026-05-23 More detailed logging, obstacle challenge fine tuning
2026-05-25 Added lost wall rescue moves
2026-05-25 Update .gitignore and enhance driveController and obstacleChallenge logic
2026-05-25 Refine obstacle detection and navigation logic in camera and gyro modules
2026-05-31 Enhance logging for color detection and obstacle avoidance in singleScanClockwise and parkCW functions
2026-06-02 Refactor camera for easyer calibration Improve parking add scanClockwiseSimulation function
2026-06-13 Enhanced local color detection calibration
